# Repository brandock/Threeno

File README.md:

# Threeno

**Threeno** is a family of through-hole, Arduino-compatible boards that came out of my own learning process as I dove deeper into low-power wireless sensor nodes. These boards were inspired by the amazing work of Jean-Claude Wippler (JeeLabs), Felix Rusu (LowPowerLab), the OpenEnergyMonitor project, Nathan Chantrell’s TinyTx, and many others. Threeno is not meant to replace any of those designs—rather, it's a personal attempt to bring together what I’ve learned from them into a format that helped me prototype and understand more deeply. They’ve been useful to me as learning tools and prototypes—and maybe they can help others explore this ecosystem, too.

I wanted a board I could use to explore this whole ecosystem—JeeLib, OpenEnergyMonitor, RFM69 radios, and the new AVR parts supported by Spence Konde's cores—but with a familiar Arduino Uno shield footprint. I didn’t want to rely on breadboards anymore. Too often, my breadboard connections were the reason things didn’t work. So Threeno took shape as a set of hand-solderable boards using plated-through-hole parts that anyone with a soldering iron could build and experiment with.

## Objectives

These design goals shaped where and how pins are broken out on the boards:

- **Familiarity**: Match the footprint of the Arduino Uno for compatibility with Uno shields and known layouts.
- **Pin Position Parity**: Line up SPI, Serial, I²C, and other common peripherals with their usual locations on the Uno.
- **Through-hole Focus**: Use PTH parts wherever possible to keep things accessible. (HopeRF radios are technically SMD, but easily hand-soldered.)
- **Proven Components**: Include parts and patterns from designs by JeeLabs, Low Power Labs, OpenEnergyMonitor, and TinyTx—such as the MCP1702 regulator and the multi-transceiver RFM footprint.
- **Stock Arduino Tooling**: Use standard Arduino board managers—no Threeno-specific tools required. ATmega328P boards use the built-in Uno target; AVR128DB28 and ATtiny84 boards use Spence Konde’s DxCore and ATTinyCore.
- **Onboard Radios**: Including the HopeRF transceivers on the board makes prototyping wireless sensors a lot easier. These parts are somewhat notoriously difficult to breadboard, so having it soldered on in a proven way takes the guess work out of that part of your prototype. Other boards, such as Felix Rusu's Moteino, also take this approach in compact and polished designs.
- **Low Power**: Use the techniques used by Rusu, JCW, and OpenEnergyMonitor to make the boards run at very low power, with single-digit uA achievable in deep sleep mode.

## Ecosystem

Threeno boards are designed to work naturally with:

- [**JeeLib**](https://github.com/jeelabs/jeelib) by Jean-Claude Wippler (JCW)
- [**OpenEnergyMonitor**](https://openenergymonitor.org/) by Glyn Hudson, Trystan Lea, Robert Wall, and many others
- [**LowPowerLab’s low-power IoT project ecosystem**](https://lowpowerlab.com) by Felix Rusu
- [**Arduino IDE**](https://www.arduino.cc/en/software) with these board cores:
  - [**DxCore**](https://github.com/SpenceKonde/DxCore) – for AVR DB series
  - [**ATtinyCore**](https://github.com/SpenceKonde/ATTinyCore) – for ATtiny84

## Threeno Alternatives

Threeno tries to fill a specific niche: a set of through-hole, hand-solderable boards with onboard radios that integrate smoothly into the JeeLib and OpenEnergyMonitor ecosystems. But depending on your needs, one of these other boards might be a better fit:

- [**Moteino**](https://lowpowerlab.com/guide/moteino/) – The original Arduino + transceiver board. If you want an Arduino UNO-compatible board with a HopeRF transciever onboard, if you were not interested in soldering your own board, and if you didn't need the classic Arduino board-shape, you would clearly choose a Moteino over a Threeno. Compact, preassembled, with a great set of shields and sketches. Part of an IoT ecosystem of its own, with a great user community and great support from Felix Rusu. You should probably just get a Moteino or two regardless. 
- [**JeeNode**](https://web.archive.org/web/20201130081805/https://jeelabs.org/docs/hardware/jnclassic/) – A classic by JCW. [You can use the JeeNode USB as a RF-to-serial gateway.](https://community.openenergymonitor.org/t/receiving-jeelib-classic-and-lowpowerlab-in-parallel/22563) JCW has numerous plugin boards with various parts and sensors. It is a clever system that is different than Arduino sheilds, and makes a ton of sense. I have a classic JeeNode and love it.
- [**Azduino**](https://azduino.com) – The latest and greatest AVR microcontrollers, on convenient breakout boards from Spence Konde, who is making the Arduino cores for them.
- [**ESP32/ESP8266**](https://en.wikipedia.org/wiki/ESP32) – Excellent for Wi-Fi/Bluetooth, though less ideal for ultra-low power, which is one of the goals of the Low Power Lab, the JeeNode, and the OpenEnergyMonitor ecosystems.
- [**EVB RFduino**](https://dwmzone.com/en/hoperf/67-657-hoperf-dk-evb-rfduino-board.html?gQT=1) - I don't know much about this board, but it is apparently an Arduino Uno-compatible board with HopeRF radio pre-assembled. So if you (a) needed the Uno footprint (so Moteino wasn't an option) (b) didn't need onboard SPI flash memory option (RFduino apparently lacks one) (c) didn't want to solder together your own kit, this might be a board to investigate.

Each of these brings something different to the table—Threeno just aims to make it easier for people (especially soldering hobbyists) to experiment in this space with familiar tools and components.

## Meet the Boards

### [Threeno Tx (ATmega328P)](ThreenoTx.md)
A classic 3.3V UNO-style board with onboard RFM69CW and FTDI or ISP programming.

### [Threeno Tiny Tx (ATtiny84)](ThreenoTinyTx.md)
Minimal and battery-friendly. Based on the ATtiny84, a nod to Nathan Chantrell’s TinyTx.

### [Threeno DB28 Tx (AVR128DB28)](ThreenoDB28.md)
A modern AVR with UPDI programming, MVIO, and Uno-compatible layout.

## Getting the Boards

- **Download Eagle files** and generate Gerbers
- **Order from Seeed Fusion**
- **Use the BOM** to order parts from DigiKey or Mouser

Each board page includes soldering guides and full part lists.

## Useful Tools

- [**FlexyTx Shield**](https://lowpowerlab.com/shop/flexytx) – Mount and test RFM69CW radios easily
- [**Evil Mad Scientist ISP Shield**](https://shop.evilmadscientist.com/productsmenu/652) – For burning bootloaders to raw AVRs

## Developing with Threeno

Use Spence Konde’s Arduino cores:

- [DxCore](https://github.com/SpenceKonde/DxCore) – for AVR128DB28
- [ATtinyCore](https://github.com/SpenceKonde/ATTinyCore) – for ATtiny84/85

For ATmega328P-based boards, select “Arduino Uno” in the IDE.

## License

This project is licensed under the GNU General Public License v3.0.

You may copy, distribute, and modify this software under the terms of the GPLv3.

See the full license at: https://www.gnu.org/licenses/gpl-3.0.en.html

---

This project is a thank you to the makers who built the boards I learned from.

– Brandon Baldock

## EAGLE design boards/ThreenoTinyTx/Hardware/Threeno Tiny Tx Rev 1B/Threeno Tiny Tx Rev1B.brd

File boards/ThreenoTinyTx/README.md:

# ThreenoTinyTx

→ **Why this board?**  _(fill in)_  
→ **Pin‑out philosophy**  _(fill in, or copy from Board‑X‑PinoutPhilosophy.md)_  
→ **Build steps**  `make gerbers` → order → solder → program → blink :)

| Quick links |
|-------------|
| [BOM & ordering notes](docs/BOM.md) |
| [Build guide](docs/Build.md) |
| [Programming steps](docs/Program.md) |
| [Variants](docs/Variants.md) |
| [Example sketches](firmware/) |

```text
hardware/   KiCad or Eagle files
firmware/   PlatformIO / Arduino sketches
docs/       Markdown docs (exported as wiki or GitHub Pages)
```

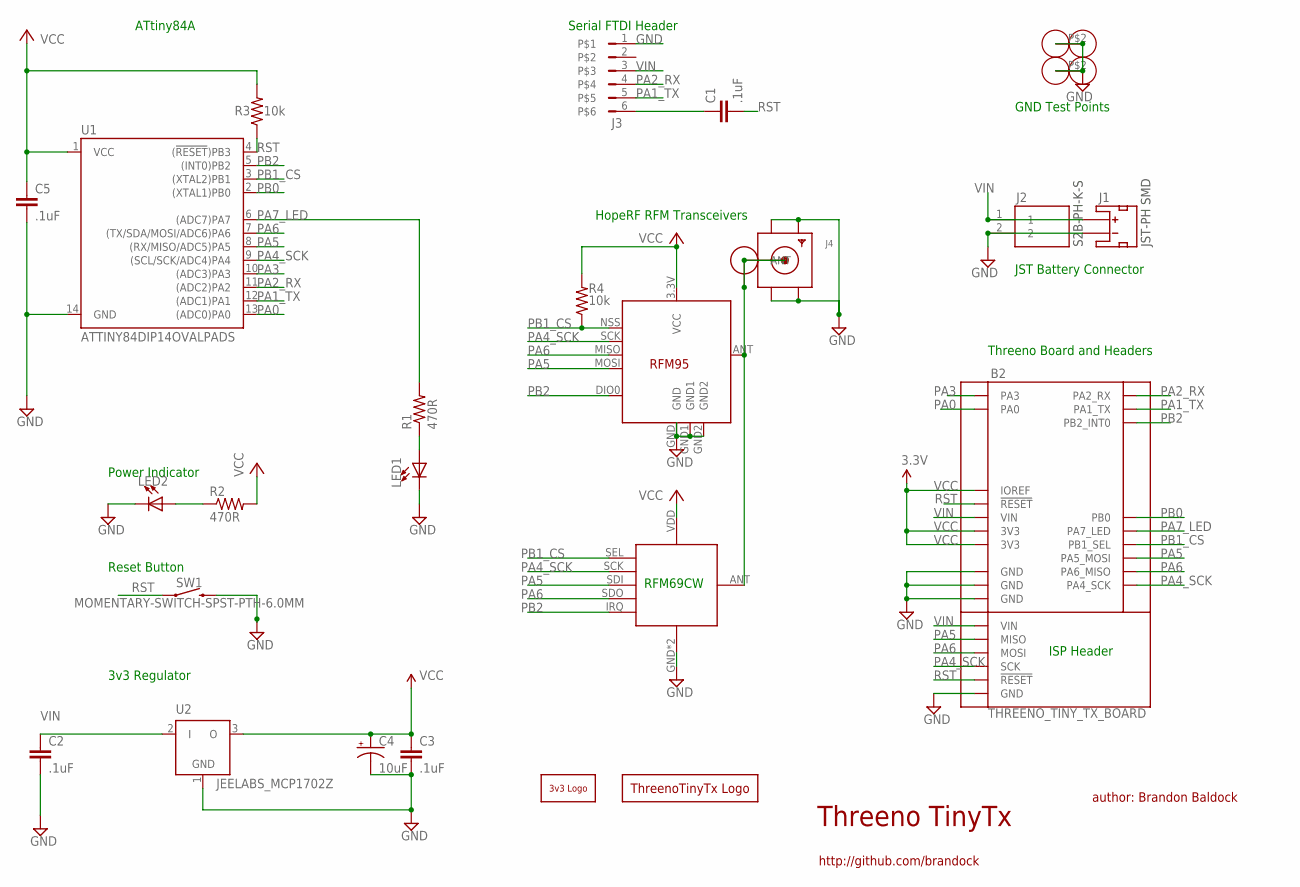
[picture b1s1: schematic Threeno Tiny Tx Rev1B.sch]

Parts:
B1: 3VTHREENO_BOTTOM_SILK
B2: THREENO_TINY_TX_BOARD
B3: THREENO_TINY_TX_LOGOTHREENO_TINY_TX_LOGO; THREENO_TINY_TX_LOGO
C1, C2, C3, C5: .1uF; C025-024X044-NO-MIDDLE-SILK
C4: 10uF; E1,8-4
J1: JST_2MM_MALE; JST-2-SMD
J2: S2B-PH-K-S; S2BPHKS
J3: FTDI; FTDI_ROUND_HEADER_SILK
J4: SMACONNECTOR_EDGE; SMA_EDGELAUNCH
J5: RFM12B_ANTENNA; RFM12B-ANTENNA
J6, J7: ALLIGATORCLIP-WIRELOOPTESTPOINT-WIRELOOP; ALLIGATORCLIP-WIRELOOP
LED1, LED2: LED-BRANDOCK3MM; LED3MM-BRANDOCK
R1, R2: 470R; 0204/7
R3, R4: 10k; 0204/7
RF1: RFM12B_MINPADS; RFM12B-MINPADS
RF2: RFM95LONGER; RFM95_LONGER
SW1: MOMENTARY-SWITCH-SPST-PTH-6.0MM; TACTILE_SWITCH_PTH_6.0MM
U1: ATTINY84DIP14OVALPADS; DIP14-OVALPADS
U2: JEELABS_MCP1702Z; JEELABS_TO92

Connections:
GND: B2.GND@1 (GND), B2.GND@2 (GND), B2.GND@3 (GND), B2.GND@ICSP (GND), C2.2, C3.2, C4.-, C5.2, J1.1 (-), J2.2, J3.1, J4.GND@1 (GND4), J4.GND@2 (GND3), J4.GND@3 (GND2), J4.GND@4 (GND1), J6.P$1, J6.P$2, J7.P$1, J7.P$2, LED1.K (C), LED2.K (C), RF1.GND, RF1.GND2 (GND), RF2.GND, RF2.GND1, RF2.GND2, SW1.3 (2), U1.14 (GND), U2.1 (GND)
unnamed: LED2.A, R2.1
unnamed: J4.P (ANT), J5.P$1, RF1.ANT, RF2.ANT
unnamed: C1.1, J3.6
unnamed: LED1.A, R1.1
PA0: B2.PA0, U1.13 ((ADC0)PA0)
PA1_TX: B2.PA1 (PA1_TX), J3.5, U1.12 ((ADC1)PA1)
PA2_RX: B2.PA2 (PA2_RX), J3.4, U1.11 ((ADC2)PA2)
PA3: B2.PA3, U1.10 ((ADC3)PA3)
PA4_SCK: B2.PA4 (PA4_SCK), B2.SCK@ICSP (SCK), RF1.SCK, RF2.SCK, U1.9 ((SCL/SCK/ADC4)PA4)
PA5: B2.MISO@ICSP (MISO), B2.PA5 (PA5_MOSI), RF1.SDI (SDI/MOSI), RF2.MOSI, U1.8 ((RX/MISO/ADC5)PA5)
PA6: B2.MOSI@ICSP (MOSI), B2.PA6 (PA6_MISO), RF1.SDO (SDO/MISO), RF2.MISO, U1.7 ((TX/SDA/MOSI/ADC6)PA6)
PA7_LED: B2.PA7 (PA7_LED), R1.2, U1.6 ((ADC7)PA7)
PB0: B2.PB0, U1.2 ((XTAL1)PB0)
PB1_CS: B2.PB1 (PB1_SEL), R4.1, RF1.SEL, RF2.NSS (SEL), U1.3 ((XTAL2)PB1)
PB2: B2.PB2 (PB2_INT0), RF1.IRQ, RF2.DIO0, U1.5 ((INT0)PB2)
RST: B2.!RESET!, B2.RESET@ICSP (!RESET!), C1.2, R3.1, SW1.1, U1.4 ((!RESET!)PB3)
VCC: B2.3.3V (3V3), B2.3.3V@2 (3V3), B2.IOREF, C3.1, C4.+, C5.1, R2.2, R3.2, R4.2, RF1.VDD, RF2.3.3V (VCC), U1.1 (VCC), U2.3 (O)
VIN: B2.VIN, B2.VIN@ICSP (VIN), C2.1, J1.2 (+), J2.1, J3.3, U2.2 (I)

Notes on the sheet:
Threeno TinyTx
author: Brandon Baldock
http://github.com/brandock
ISP Header
JST-PH SMD
S2B-PH-K-S
JST Battery Connector
RFM69CW
Power Indicator
Reset Button
3v3 Regulator
ATtiny84A
Threeno Board and Headers
HopeRF RFM Transceivers
Serial FTDI Header
GND Test Points

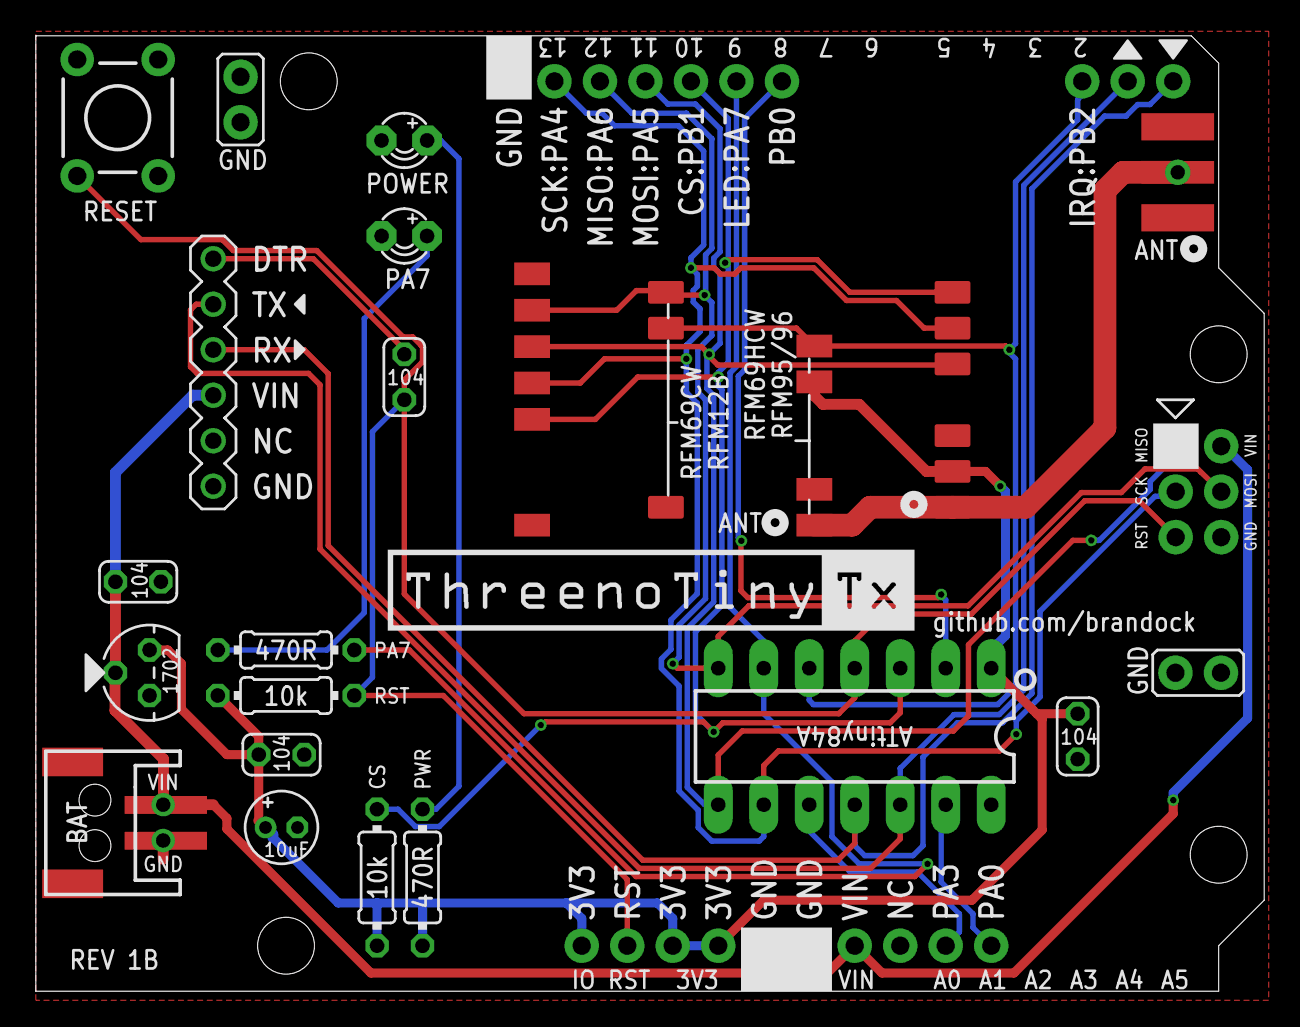
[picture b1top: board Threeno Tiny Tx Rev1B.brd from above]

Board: 2 copper layers, 68.6 x 53.3 mm, 26 parts (0 on the bottom side), 19 nets.

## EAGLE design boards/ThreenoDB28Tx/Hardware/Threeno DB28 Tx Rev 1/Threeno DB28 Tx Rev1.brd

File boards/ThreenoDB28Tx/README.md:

# ThreenoDB28Tx

→ **Why this board?**  _(fill in)_  
→ **Pin‑out philosophy**  _(fill in, or copy from Board‑X‑PinoutPhilosophy.md)_  
→ **Build steps**  `make gerbers` → order → solder → program → blink :)

| Quick links |
|-------------|
| [BOM & ordering notes](docs/BOM.md) |
| [Build guide](docs/Build.md) |
| [Programming steps](docs/Program.md) |
| [Variants](docs/Variants.md) |
| [Example sketches](firmware/) |

```text
hardware/   KiCad or Eagle files
firmware/   PlatformIO / Arduino sketches
docs/       Markdown docs (exported as wiki or GitHub Pages)
```

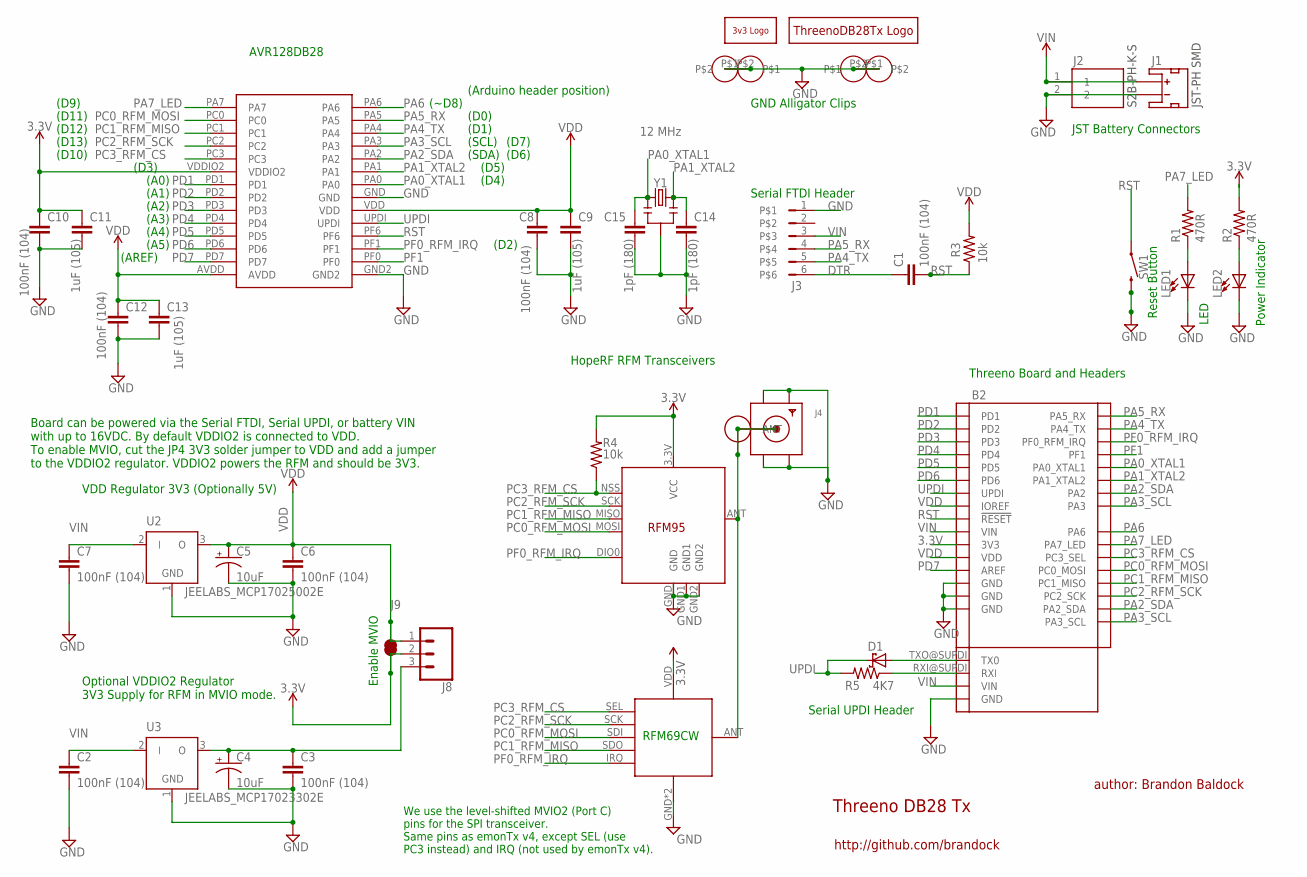
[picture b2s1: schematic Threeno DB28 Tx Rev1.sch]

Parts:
B1: 3VTHREENO_BOTTOM_SILK
B2: THREENO_DB28_TX_BOARD_V1.1
B3: THREENO_DB28_TX_LOGO
C1, C2, C3, C6, C7, C8, C10, C12: 100nF (104); C025-024X044-NO-MIDDLE-SILK
C4, C5: 10uF; E1,8-4
C9, C11, C13: 1uF (105); C025-024X044-NO-MIDDLE-SILK
C14, C15: 1pF (180); C025-024X044-NO-MIDDLE-SILK
D1: DIODE SCHOTTKY 30V 200MA DO35; DO41-7
J1: JST_2MM_MALE; JST-2-SMD
J2: S2B-PH-K-S; S2BPHKS
J3: FTDI; FTDI_ROUND_HEADER_SILK
J4: SMACONNECTOR_EDGE; SMA_EDGELAUNCH
J5: RFM12B_ANTENNA; RFM12B-ANTENNA
J6, J7: ALLIGATORCLIP-WIRELOOP
J8: 455-1750-1-ND; 1X03
J9: JUMPER-SMT_2_NC_TRACE_24_MIL_NO-SILK; SMT-JUMPER_2_NC_TRACE_NO-SILK_24_MIL
LED1, LED2: LED-BRANDOCK3MM; LED3MM-BRANDOCK
R1, R2: 470R; 0204/7
R3, R4: 10k; 0204/7
R5: 4K7; 0204/7
RF1: RFM12B_MINPADS; RFM12B-MINPADS
RF2: RFM95LONGER; RFM95_LONGER
SW1: MOMENTARY-SWITCH-SPST-PTH-6.0MM; TACTILE_SWITCH_PTH_6.0MM
U1: AVR128DB28; DIL28-3
U2: JEELABS_MCP17025002E; JEELABS_TO92
U3: JEELABS_MCP17023302E; JEELABS_TO92
Y1: 12 MHz; HC49US-OR-RESONATOR

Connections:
3.3V: B2.3.3V (3V3), C10.1, C11.1, J8.2, J9.2, R2.2, R4.2, RF1.VDD, RF2.3.3V (VCC), U1.VDDIO2
DTR: C1.1, J3.6
GND: B2.GND@1 (GND), B2.GND@2 (GND), B2.GND@3 (GND), B2.GND@SUPDI (GND), C2.2, C3.2, C4.-, C5.-, C6.2, C7.2, C8.2, C9.2, C10.2, C11.2, C12.2, C13.2, C14.2, C15.2, J1.1 (-), J2.2, J3.1, J4.GND@1 (GND4), J4.GND@2 (GND3), J4.GND@3 (GND2), J4.GND@4 (GND1), J6.P$1, J6.P$2, J7.P$1, J7.P$2, LED1.K (C), LED2.K (C), RF1.GND, RF1.GND2 (GND), RF2.GND, RF2.GND1, RF2.GND2, SW1.3 (2), U1.GND, U1.GND2, U2.1 (GND), U3.1 (GND), Y1.2
unnamed: LED2.A, R2.1
unnamed: J4.P (ANT), J5.P$1, RF1.ANT, RF2.ANT
unnamed: B2.RXI@SUPDI (RXI), R5.1
unnamed: B2.TXO@SUPDI (TX0), D1.A
unnamed: C3.1, C4.+, J8.3, U3.3 (O)
unnamed: LED1.A, R1.1
PA0_XTAL1: B2.PA0 (PA0_XTAL1), C15.1, U1.PA0, Y1.1
PA1_XTAL2: B2.PA1 (PA1_XTAL2), C14.1, U1.PA1, Y1.3
PA2_SDA: B2.PA2, B2.PA2|SDA (PA2_SDA), U1.PA2
PA3_SCL: B2.PA3, B2.PA3|SCL (PA3_SCL), U1.PA3
PA4_TX: B2.PA4|TX (PA4_TX), J3.5, U1.PA4
PA5_RX: B2.PA5|RX (PA5_RX), J3.4, U1.PA5
PA6: B2.PA6, U1.PA6
PA7_LED: B2.PA7 (PA7_LED), R1.2, U1.PA7
PC0_RFM_MOSI: B2.PC0 (PC0_MOSI), RF1.SDI (SDI/MOSI), RF2.MOSI, U1.PC0
PC1_RFM_MISO: B2.PC1 (PC1_MISO), RF1.SDO (SDO/MISO), RF2.MISO, U1.PC1
PC2_RFM_SCK: B2.PC2 (PC2_SCK), RF1.SCK, RF2.SCK, U1.PC2
PC3_RFM_CS: B2.PC3 (PC3_SEL), R4.1, RF1.SEL, RF2.NSS (SEL), U1.PC3
PD1: B2.PD1|A0 (PD1), U1.PD1
PD2: B2.PD2|A1 (PD2), U1.PD2
PD3: B2.PD3|A2 (PD3), U1.PD3
PD4: B2.PD4|A3 (PD4), U1.PD4
PD5: B2.PD5|A4 (PD5), U1.PD5
PD6: B2.PD6|A5 (PD6), U1.PD6
PD7: B2.PD7 (AREF), U1.PD7
PF0_RFM_IRQ: B2.PF0 (PF0_RFM_IRQ), RF1.IRQ, RF2.DIO0, U1.PF1
PF1: B2.PF1, U1.PF0
RST: B2.RESET@1 (!RESET!), C1.2, R3.1, SW1.1, U1.PF6
UPDI: B2.NC (UPDI), D1.C, R5.2, U1.UPDI
VDD: B2.VDD, B2.VDD|IOREF (IOREF), C5.+, C6.1, C8.1, C9.1, C12.1, C13.1, J8.1, J9.1, R3.2, U1.AVDD, U1.VDD, U2.3 (O)
VIN: B2.VIN, B2.VIN@SUPDI (VIN), C2.1, C7.1, J1.2 (+), J2.1, J3.3, U2.2 (I), U3.2 (I)

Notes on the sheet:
Threeno DB28 Tx
author: Brandon Baldock
http://github.com/brandock
Serial UPDI Header
JST-PH SMD
S2B-PH-K-S
JST Battery Connectors
RFM69CW
Power Indicator
Reset Button
Optional VDDIO2 Regulator 3V3 Supply for RFM in MVIO mode.
AVR128DB28
Threeno Board and Headers
HopeRF RFM Transceivers
Serial FTDI Header
(Arduino header position)
(D10)
(D9)
(D12)
(D11)
(D13)
(A0)
(A1)
We use the level-shifted MVIO2 (Port C) pins for the SPI transceiver. Same pins as emonTx v4, except SEL (use PC3 instead) and IRQ (not used by emonTx v4).
VDD Regulator 3V3 (Optionally 5V)
LED
(A2)
(A3)
(A4)
(AREF)
(SDA)
(SCL)
(~D8)
(D2)
(A5)
(D4)
(D6)
(D7)
Board can be powered via the Serial FTDI, Serial UPDI, or battery VIN with up to 16VDC. By default VDDIO2 is connected to VDD. To enable MVIO, cut the JP4 3V3 solder jumper to VDD and add a jumper to the VDDIO2 regulator. VDDIO2 powers the RFM and should be 3V3.
Enable MVIO

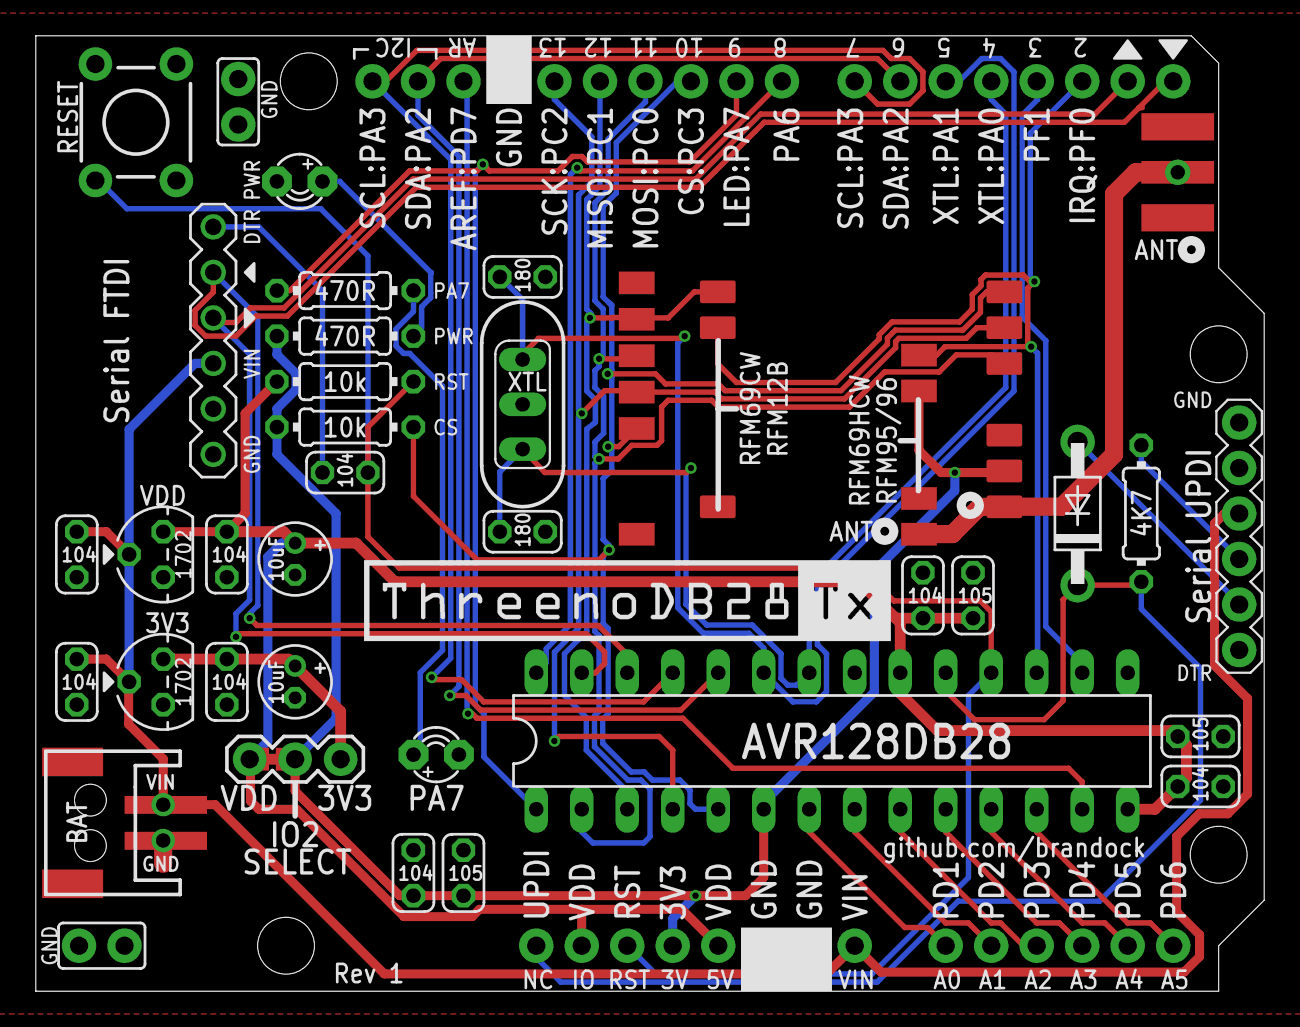
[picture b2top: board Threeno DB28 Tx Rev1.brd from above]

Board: 2 copper layers, 68.6 x 53.3 mm, 42 parts (0 on the bottom side), 34 nets.

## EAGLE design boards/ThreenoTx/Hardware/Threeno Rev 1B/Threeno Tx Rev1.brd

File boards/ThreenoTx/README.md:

# ThreenoTx

→ **Why this board?**  _(fill in)_  
→ **Pin‑out philosophy**  _(fill in, or copy from Board‑X‑PinoutPhilosophy.md)_  
→ **Build steps**  `make gerbers` → order → solder → program → blink :)

| Quick links |
|-------------|
| [BOM & ordering notes](docs/BOM.md) |
| [Build guide](docs/Build.md) |
| [Programming steps](docs/Program.md) |
| [Variants](docs/Variants.md) |
| [Example sketches](firmware/) |

```text
hardware/   KiCad or Eagle files
firmware/   PlatformIO / Arduino sketches
docs/       Markdown docs (exported as wiki or GitHub Pages)
```

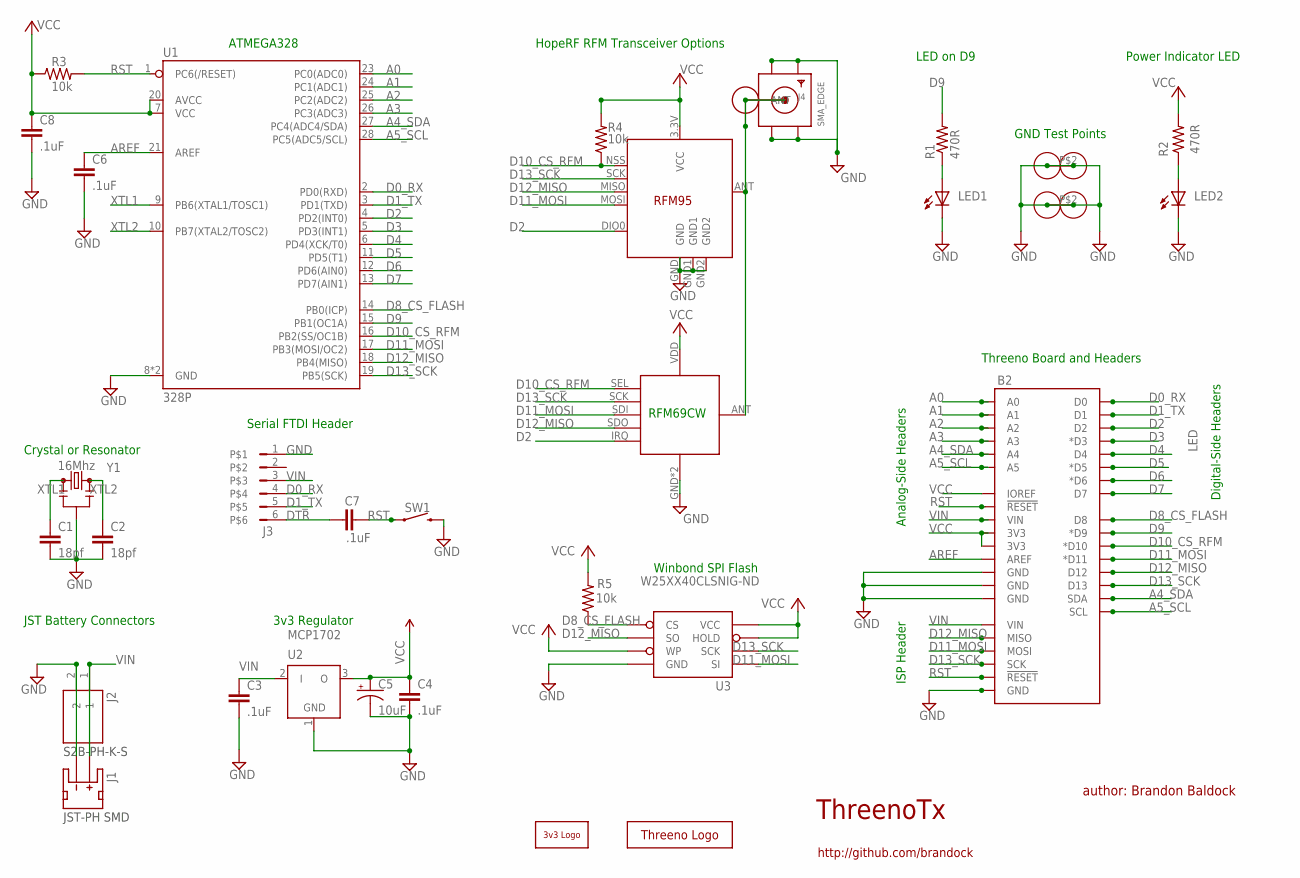
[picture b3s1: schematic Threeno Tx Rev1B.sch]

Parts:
B1: 3VTHREENO_BOTTOM_SILK
B2: THREENO_TX_BOARD3VTHREENO; THREENO_TX_BOARD
B3: 3VTHREENO_LOGO
C1, C2: 18pf; C025-024X044-NO-MIDDLE-SILK
C3, C4, C6, C7, C8: .1uF; C025-024X044-NO-MIDDLE-SILK
C5: 10uF; E1,8-4
J1: JST-PH-SMD; JST-2-SMD
J2: S2B-PH-K-S; S2BPHKS
J3: FTDI; FTDI_ROUND_HEADER_SILK
J4: SMA_EDGE; SMA_EDGELAUNCH
J5: RFM12B_ANTENNA; RFM12B-ANTENNA
J6, J7: ALLIGATORCLIP-WIRELOOP
LED1, LED2: LED; LED3MM-BRANDOCK
R1, R2: 470R; 0204/7
R3, R4, R5: 10k; 0204/7
RF1: RFM12B_MINPADS; RFM12B-MINPADS
RF2: RFM95LONGER; RFM95_LONGER
SW1: MOMENTARY-SWITCH-SPST-PTH-6.0MM; TACTILE_SWITCH_PTH_6.0MM
U1: 328P; DIP28-OVALPADS
U2: JEELABS_MCP1702Z; JEELABS_TO92
U3: AT25F512BJEDEC_3.9MM; SO08
Y1: 16Mhz; HC49US-OR-RESONATOR

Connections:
A0: B2.A0, U1.23 (PC0(ADC0))
A1: B2.A1, U1.24 (PC1(ADC1))
A2: B2.A2, U1.25 (PC2(ADC2))
A3: B2.A3, U1.26 (PC3(ADC3))
A4_SDA: B2.A4, B2.SDA, U1.27 (PC4(ADC4/SDA))
A5_SCL: B2.A5, B2.SCL, U1.28 (PC5(ADC5/SCL))
AREF: B2.AREF, C6.1, U1.21 (AREF)
D0_RX: B2.D0, J3.4, U1.2 (PD0(RXD))
D1_TX: B2.D1, J3.5, U1.3 (PD1(TXD))
D2: B2.D2, RF1.IRQ, RF2.DIO0, U1.4 (PD2(INT0))
D3: B2.D3 (*D3), U1.5 (PD3(INT1))
D4: B2.D4, U1.6 (PD4(XCK/T0))
D5: B2.D5 (*D5), U1.11 (PD5(T1))
D6: B2.D6 (*D6), U1.12 (PD6(AIN0))
D7: B2.D7, U1.13 (PD7(AIN1))
D8_CS_FLASH: B2.D8, R5.1, U1.14 (PB0(ICP)), U3.1_CS (CS)
D9: B2.D9 (*D9), R1.2, U1.15 (PB1(OC1A))
D10_CS_RFM: B2.D10 (*D10), R4.1, RF1.SEL, RF2.NSS (SEL), U1.16 (PB2(SS/OC1B))
D11_MOSI: B2.D11 (*D11), B2.MOSI@ICSP (MOSI), RF1.SDI (SDI/MOSI), RF2.MOSI, U1.17 (PB3(MOSI/OC2)), U3.5_SI (SI)
D12_MISO: B2.D12, B2.MISO@ICSP (MISO), RF1.SDO (SDO/MISO), RF2.MISO, U1.18 (PB4(MISO)), U3.2_SO (SO)
D13_SCK: B2.D13, B2.SCK@ICSP (SCK), RF1.SCK, RF2.SCK, U1.19 (PB5(SCK)), U3.6_SCK (SCK)
DTR: C7.1, J3.6
GND: B2.GND@1 (GND), B2.GND@2 (GND), B2.GND@3 (GND), B2.GND@ICSP (GND), C1.2, C2.2, C3.2, C4.2, C5.-, C6.2, C8.2, J1.1 (-), J2.2, J3.1, J4.GND@1 (GND4), J4.GND@2 (GND3), J4.GND@3 (GND2), J4.GND@4 (GND1), J6.P$1, J6.P$2, J7.P$1, J7.P$2, LED1.K (C), LED2.K (C), RF1.GND, RF1.GND2 (GND), RF2.GND, RF2.GND1, RF2.GND2, SW1.3 (2), U1.8 (GND), U1.22 (GND), U2.1 (GND), U3.4_GND (GND), Y1.2
unnamed: LED2.A, R2.1
unnamed: J4.P (ANT), J5.P$1, RF1.ANT, RF2.ANT
unnamed: LED1.A, R1.1
RST: B2.RESET@1 (!RESET!), B2.RESET@ICSP (!RESET!), C7.2, R3.2, SW1.1, U1.1 (PC6(/RESET))
VCC: B2.3.3V (3V3), B2.3.3V@2 (3V3), B2.IOREF, C4.1, C5.+, C8.1, R2.2, R3.1, R4.2, R5.2, RF1.VDD, RF2.3.3V (VCC), U1.7 (VCC), U1.20 (AVCC), U2.3 (O), U3.3_WP (WP), U3.7_HOLD (HOLD), U3.8_VCC (VCC)
VIN: B2.VIN, B2.VIN@ICSP (VIN), C3.1, J1.2 (+), J2.1, J3.3, U2.2 (I)
XTL1: C1.1, U1.9 (PB6(XTAL1/TOSC1)), Y1.1
XTL2: C2.1, U1.10 (PB7(XTAL2/TOSC2)), Y1.3

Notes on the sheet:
ThreenoTx
author: Brandon Baldock
http://github.com/brandock
ISP Header
JST-PH SMD
S2B-PH-K-S
JST Battery Connectors
RFM69CW
Power Indicator LED
3v3 Regulator
ATMEGA328
Threeno Board and Headers
Analog-Side Headers
Digital-Side Headers
HopeRF RFM Transceiver Options
Serial FTDI Header
GND Test Points
LED on D9
Crystal or Resonator
Winbond SPI Flash

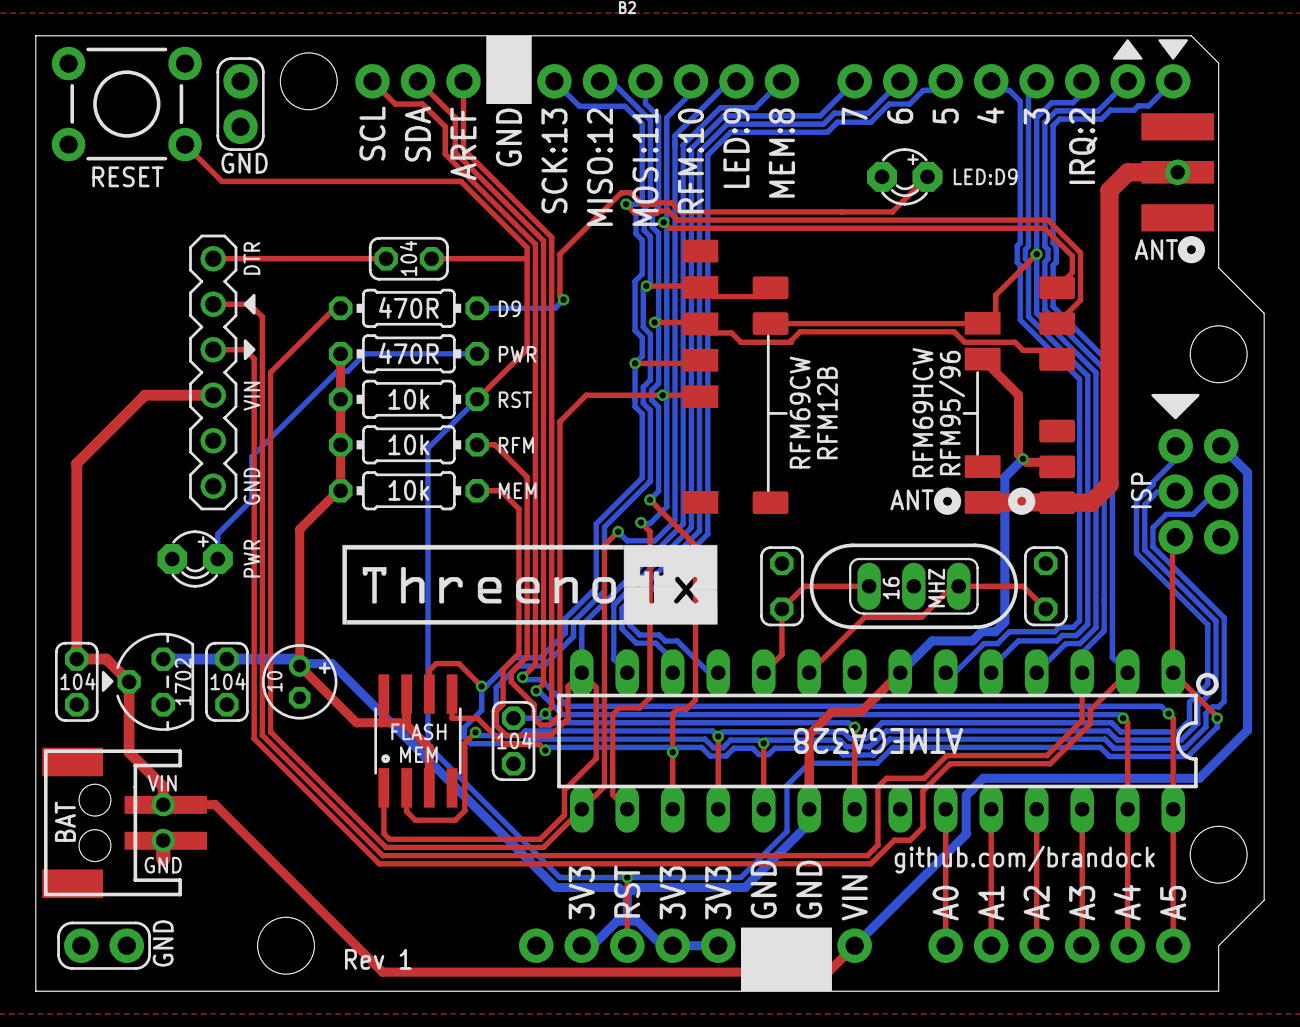
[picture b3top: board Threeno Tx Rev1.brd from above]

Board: 2 copper layers, 68.6 x 53.3 mm, 31 parts (0 on the bottom side), 31 nets.

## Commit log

2025-04-22 Initial Threeno repo scaffold – boards, docs, ignore, licence
2025-04-22 Deployed 250a785 with MkDocs version: 1.6.1
2025-04-22 Update LICENSE
2025-04-30 Create Hardware Folder
2025-04-30 Create Rev 1B
2025-04-30 Create Threeno Rev 1B Directory

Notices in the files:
parts and their libraries:
SparkFun-Connectors: Licensing: CC v3.0 Share-Alike You are welcome to use this library for commercial purposes.
SparkFun-Switches: Licensing: Creative Commons ShareAlike 4.0 International - https://creativecommons.org/licenses/by-sa/4.0
